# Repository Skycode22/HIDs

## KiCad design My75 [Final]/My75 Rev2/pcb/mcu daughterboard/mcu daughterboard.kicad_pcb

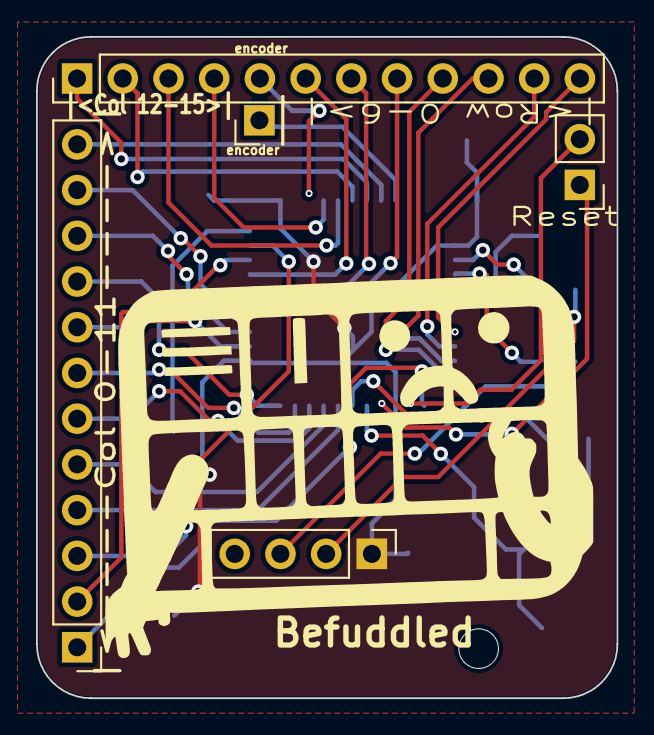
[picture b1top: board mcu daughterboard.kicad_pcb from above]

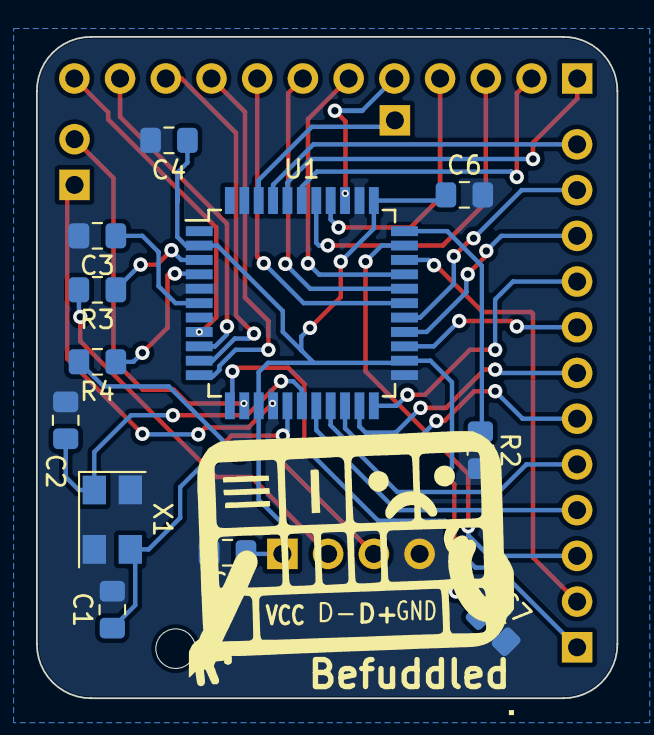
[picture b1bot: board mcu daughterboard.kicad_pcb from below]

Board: 2 copper layers, 32.2 x 36.7 mm, 17 parts (12 on the bottom side), 35 nets.

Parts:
*: '; PinHeader_1x04_P2.54mm_Vertical
*#2: '; PinHeader_1x01_P2.54mm_Vertical
*#3: PinHeader_1x02_P2.54mm_Vertical
*#4: 1; PinHeader_1x12_P2.54mm_Vertical
*#5: '; PinHeader_1x12_P2.54mm_Vertical
C1, C2, C3, C4, C5, C6, C7: 22pF; C_0805_2012Metric_Pad1.15x1.40mm_HandSolder
R2: 10k; R_0805_2012Metric_Pad1.15x1.40mm_HandSolder
R3, R4: 22; R_0805_2012Metric_Pad1.15x1.40mm_HandSolder
U1: ATMEGA32U4; TQFP-44_10x10mm_P0.8mm
X1: XTAL_GND; Crystal_SMD_5032-4Pin_5.0x3.2mm

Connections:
/col0: *#5.1, U1.12
/col1: *#5.2, U1.31
/col2: *#5.3, U1.32
/col3: *#5.4, U1.18
/col4: *#5.5, U1.19
/col5: *#5.6, U1.20
/col6: *#5.7, U1.21
/col7: *#5.8, U1.25
/col8: *#5.9, U1.22
/col9: *#5.10, U1.26
/col10: *#5.11, U1.27
/col11: *#5.12, U1.41
/col12: *#4.1, U1.40
/col13: *#4.2, U1.39
/col14: *#4.3, U1.38
/col15: *#4.4, U1.37
/row0: *#4.12, U1.8
/row1: *#4.11, U1.9
/row2: *#4.10, U1.10
/row3: *#4.9, U1.11
/row4: *#4.8, U1.28
/row5: *#4.7, U1.29
/row6: *#4.6, U1.30
GND: *.4, C1.2, C2.2, C3.2, C4.2, C5.2, C6.2, C7.2, R2.2, U1.5, U1.15, U1.23, U1.35, U1.43, X1.2, X1.4
unnamed: C1.1, U1.16, X1.1
unnamed: C2.1, U1.17, X1.3
unnamed: C3.1, U1.6
unnamed: R2.1, U1.33
unnamed: R3.1, U1.3
unnamed: R4.1, U1.4
unnamed: *#2.1, U1.42
unnamed: *#4.5, U1.36
unnamed: *.2, R3.2
unnamed: *.3, R4.2
VCC: *.1, C4.1, C5.1, C6.1, C7.1, U1.2, U1.14, U1.24, U1.34
